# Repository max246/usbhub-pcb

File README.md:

# Opensource USB Hub PCB

I was looking to make a custom USB Hub for a project but I couldnt find any of them that worked and using the chip GL850G.
The chip is pretty old and cheap, but in my case I didnt need to use any of the fast transfering USB3, probably the next version can be based on this schematic.

I have took the schematic from a chinese website and re-written on eagle + designed the PCB, which is not the best compact and neat design but it worked as prototype.

I am offering all the files and part lists in case someone will want to make a custom USB Hub.

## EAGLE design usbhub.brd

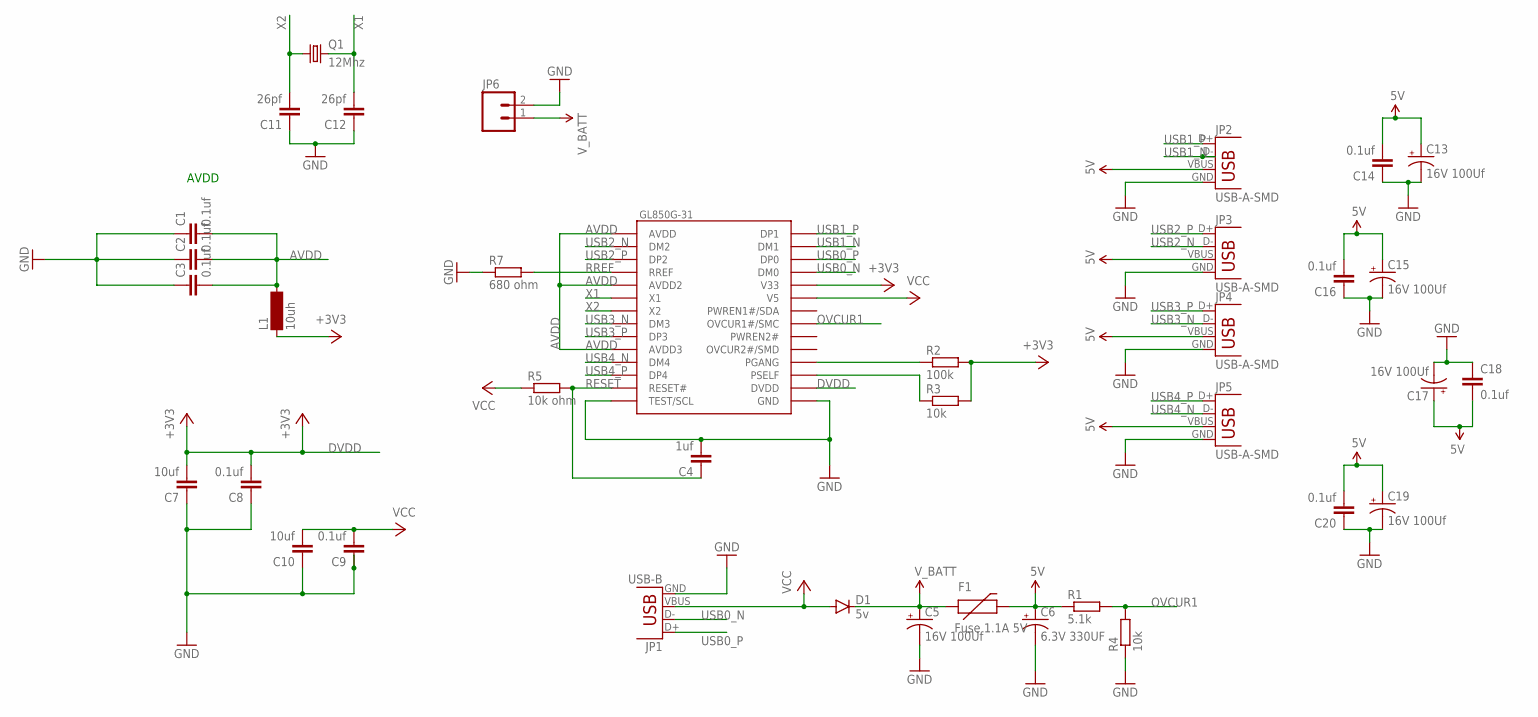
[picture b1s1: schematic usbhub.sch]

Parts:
C1, C2, C3, C8, C9, C14, C16, C18, C20: 0.1uf; C1206; MPN MCSH31B104K500CT
C4: 1uf; C1206; MPN 12061C105KAT2A
C5, C13, C15, C17, C19: 16V 100Uf; PANASONIC_D; MPN EEEHA1C101WP
C6: 6.3V 330UF; PANASONIC_D; MPN EEEHC0J331P
C7, C10: 10uf; C1206; MPN C1206C106K3PACTU
C11, C12: 26pf; C1206; MPN 12061A220JAT2A
D1: 5v; SMA-DIODE_ALT; MPN SMAJ5.0A
F1: Fuse 1.1A 5V; PTC-1206; MPN MICROSMD110F-2
JP1: USB-B; USB-B-PTH; MPN 292304-1
JP2, JP3, JP4, JP5: USB-A-SMD; USB-A-S-NOSILK-FEMALE
JP6: M02LOCK_LONGPADS; 1X02_LOCK_LONGPADS
L1: 10uh; SM-1206; MPN PFL3215-103MEB
Q1: 12Mhz; CTS406; MPN ABM3B-12.000MHZ-B2-T
R1: 5.1k; M1206; MPN CRCW12065K10FKEA.
R2: 100k; M1206; MPN WCR1206-100KFI
R3, R4: 10k; M1206; MPN MCMR12X1002FTL
R5: 10k ohm; M1206; MPN MCMR12X1002FTL
R7: 680 ohm; M1206; MPN WCR1206-680RFI
U$1: GL850G-31; TSSOP28

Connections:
5V: C6.+, C13.+, C14.2, C15.+, C16.2, C17.+, C18.2, C19.+, C20.2, F1.2, JP2.VBUS, JP3.VBUS, JP4.VBUS, JP5.VBUS, R1.1
+3V3: L1.1, R2.2, R3.2, U$1.24 (V33)
AVDD: C1.2, C2.2, C3.2, L1.2, U$1.1 (AVDD), U$1.5 (AVDD2), U$1.10 (AVDD3)
DVDD: C7.2, C8.2, U$1.16 (DVDD)
GND: C1.1, C2.1, C3.1, C4.2, C5.-, C6.-, C7.1, C8.1, C9.1, C10.1, C11.1, C12.1, C13.-, C14.1, C15.-, C16.1, C17.-, C18.1, C19.-, C20.1, JP1.GND, JP2.GND, JP3.GND, JP4.GND, JP5.GND, JP6.2, R4.1, R7.1, U$1.14 (TEST/SCL), U$1.15 (GND)
unnamed: R2.1, U$1.18 (PGANG)
unnamed: R3.1, U$1.17 (PSELF)
OVCUR1: R1.2, R4.2, U$1.21 (OVCUR1#/SMC)
RESET: C4.1, R5.2, U$1.13 (RESET#)
RREF: R7.2, U$1.4 (RREF)
USB0_N: JP1.D-, U$1.25 (DM0)
USB0_P: JP1.D+, U$1.26 (DP0)
USB1_N: JP2.D-, U$1.27 (DM1)
USB1_P: JP2.D+, U$1.28 (DP1)
USB2_N: JP3.D-, U$1.2 (DM2)
USB2_P: JP3.D+, U$1.3 (DP2)
USB3_N: JP4.D-, U$1.8 (DM3)
USB3_P: JP4.D+, U$1.9 (DP3)
USB4_N: JP5.D-, U$1.11 (DM4)
USB4_P: JP5.D+, U$1.12 (DP4)
VCC: C9.2, C10.2, D1.A, JP1.VBUS, R5.1, U$1.23 (V5)
V_BATT: C5.+, D1.C, F1.1, JP6.1
X1: C12.2, Q1.3 (2), U$1.6 (X1)
X2: C11.2, Q1.1, U$1.7 (X2)

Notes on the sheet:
AVDD

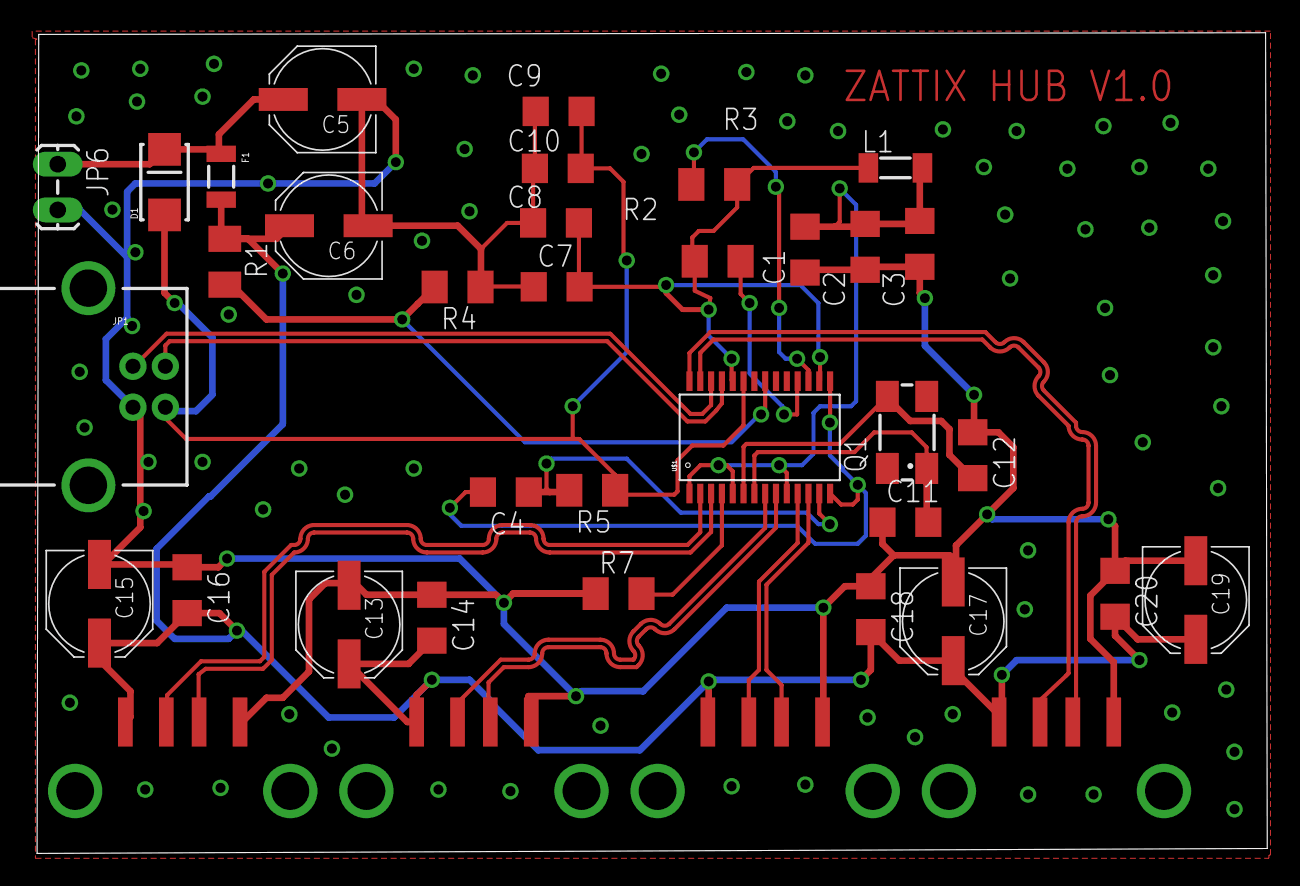
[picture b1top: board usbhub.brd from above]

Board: 2 copper layers, 75.1 x 50.1 mm, 37 parts (0 on the bottom side), 24 nets.

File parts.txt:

Partlist

Exported from usbhub.brd at 21/08/2016 19:15

EAGLE Version 7.5.0 Copyright (c) 1988-2015 CadSoft

Assembly variant: 

Part     Value          Package               Library               Position (mm)         Orientation

C1       0.1uf          C1206                 rcl                   (46.88 36.86)         R90
C2       0.1uf          C1206                 rcl                   (50.55 37.03)         R90
C3       0.1uf          C1206                 rcl                   (53.89 37.21)         R90
C4       1uf            C1206                 rcl                   (28.62 22.06)         R180
C5       16V 100Uf      PANASONIC_D           SparkFun-Passives     (17.43 46.03)         R180
C6       6.3V 330UF     PANASONIC_D           SparkFun-Passives     (17.81 38.32)         R180
C7       10uf           C1206                 rcl                   (31.72 34.59)         R0
C8       0.1uf          C1206                 rcl                   (31.68 38.49)         R0
C9       0.1uf          C1206                 rcl                   (31.84 45.3)          R0
C10      10uf           C1206                 rcl                   (31.79 41.82)         R0
C11      26pf           C1206                 rcl                   (53.01 20.22)         R0
C12      26pf           C1206                 rcl                   (57.12 24.31)         R270
C13      16V 100Uf      PANASONIC_D           SparkFun-Passives     (19.05 13.97)         R270
C14      0.1uf          C1206                 rcl                   (24.1 14.39)          R270
C15      16V 100Uf      PANASONIC_D           SparkFun-Passives     (3.81 15.24)          R270
C16      0.1uf          C1206                 rcl                   (9.16 16.07)          R270
C17      16V 100Uf      PANASONIC_D           SparkFun-Passives     (55.93 14.17)         R270
C18      0.1uf          C1206                 rcl                   (50.9 14.91)          R270
C19      16V 100Uf      PANASONIC_D           SparkFun-Passives     (70.74 15.47)         R270
C20      0.1uf          C1206                 rcl                   (65.81 15.85)         R270
D1       5v             SMA-DIODE_ALT         SparkFun-DiscreteSemi (7.78 40.98)          R90
F1       Fuse 1.1A 5V   PTC-1206              SparkFun-PowerIC      (11.24 41.31)         R270
JP1      USB-B          USB-B-PTH             SparkFun-Connectors   (5.85 28.49)          R0
JP2      USB-A-SMD      USB-A-S-NOSILK-FEMALE SparkFun-Connectors   (62.23 3.81)          R90
JP3      USB-A-SMD      USB-A-S-NOSILK-FEMALE SparkFun-Connectors   (8.89 3.81)           R90
JP4      USB-A-SMD      USB-A-S-NOSILK-FEMALE SparkFun-Connectors   (26.67 3.81)          R90
JP5      USB-A-SMD      USB-A-S-NOSILK-FEMALE SparkFun-Connectors   (44.45 3.81)          R90
JP6                     1X02_LOCK_LONGPADS    SparkFun-Connectors   (1.26 41.95)          R270
L1       10uh           SM-1206               inductor-neosid       (52.4 41.85)          R0
Q1       12Mhz          CTS406                crystal               (53.11 25.7)          R90
R1       5.1k           M1206                 rcl                   (11.46 36.12)         R270
R2       100k           M1206                 rcl                   (41.55 36.15)         R180
R3       10k            M1206                 rcl                   (41.34 40.84)         R0
R4       10k            M1206                 rcl                   (25.67 34.58)         R180
R5       10k ohm        M1206                 rcl                   (33.89 22.17)         R180
R7       680 ohm        M1206                 rcl                   (35.5 15.86)          R0
U$1      GL850G-31      TSSOP28               pimoroni              (44.45 25.4)          R90

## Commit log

2016-08-21 add files

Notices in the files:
parts and their libraries:
SparkFun-Passives: Licensing: Creative Commons ShareAlike 4.0 International - https://creativecommons.org/licenses/by-sa/4.0
pimoroni: Licensing: CC v3.0 Share-Alike You are welcome to use this library for commercial purposes.
